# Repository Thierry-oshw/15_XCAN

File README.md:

# Can controller and CAN transceiver module

Can module to easily add CAN support to anything with SPI

[Link for controller](https://github.com/Thierry-oshw/17_CAN_Controller)

[Link for transceiver](https://github.com/Thierry-oshw/15_XCAN)

## Features
- Small (Controller is 18x20 mm, Transceiver is 17x15 mm)
- Cheap (2 layer and components on one side)
- 2.54 header + castellated pad for direct board to board soldering

## Made with

- [Kicad V6](https://www.kicad.org/)

## Schematic

### 15 XCAN Schematic

### 17 CAN Controller Schematic

## Build the PCB

PCB has been fully tested on multiple projects

[CAN Controller build files](https://github.com/Thierry-oshw/17_CAN_Controller/tree/main/fabrication_2023_04_23)

[CAN Transceiver build files without castellated holes](https://github.com/Thierry-oshw/15_XCAN/tree/main/fabrication_2023_04_21)

[CAN Transceiver build files with castellated holes](https://github.com/Thierry-oshw/15_XCAN/tree/main/fabrication_2023_04_21_CH)

## Authors

- Thierry Orlandi ([Hardware Freelance](https://www.linkedin.com/in/thierry-orlandi))
- Yohann Belair ([R&D Freelance](https://github.com/ciborg971))

## License
[CERN Open Hardware Licence Version 2](https://github.com/Thierry-oshw/15_XCAN/blob/main/LICENSE.txt)

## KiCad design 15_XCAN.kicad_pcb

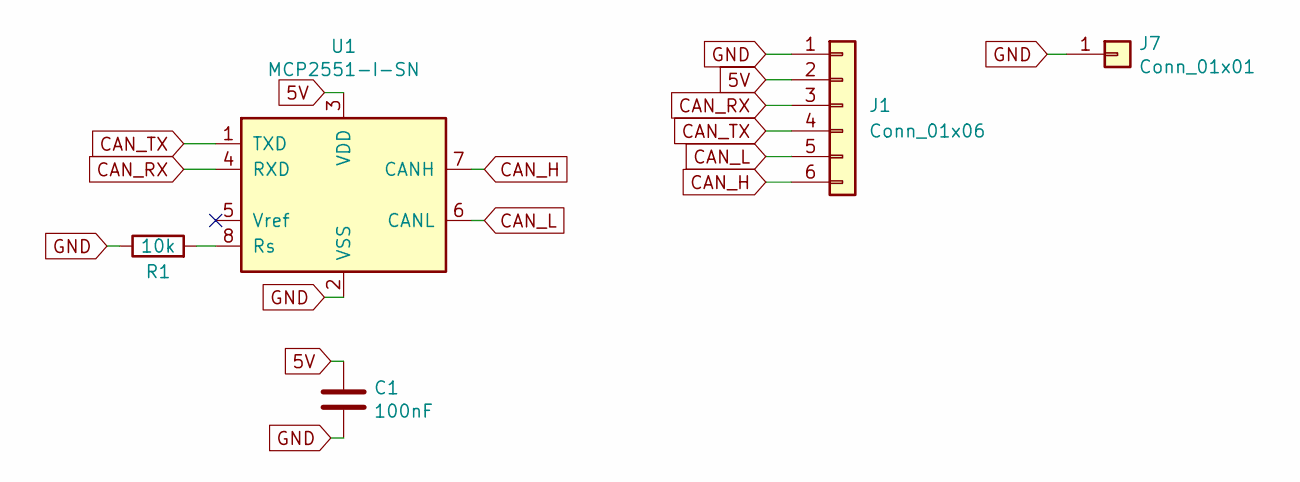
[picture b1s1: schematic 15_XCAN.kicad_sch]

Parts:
C1: 100nF; C_0603_1608Metric; LCSC C14663
J1: Conn_01x06; PinHeader_1x06_P2.54mm_Vertical
J7: Conn_01x01; PinHeader_1x01_P2.54mm_Vertical
R1: 10k; R_0603_1608Metric_Pad1.05x0.95mm_HandSolder; LCSC C25804
U1: MCP2551-I-SN; SOIC-8_3.9x4.9mm_P1.27mm; LCSC C49558

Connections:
5V: C1.1, J1.2, U1.3 (VDD)
CAN_H: J1.6, U1.7 (CANH)
CAN_L: J1.5, U1.6 (CANL)
CAN_RX: J1.3, U1.4 (RXD)
CAN_TX: J1.4, U1.1 (TXD)
GND: C1.2, J1.1, J7.1, R1.1, U1.2 (VSS)
unnamed: R1.2, U1.8 (Rs)

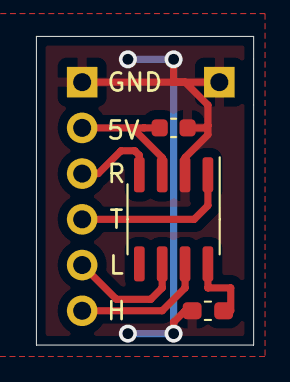
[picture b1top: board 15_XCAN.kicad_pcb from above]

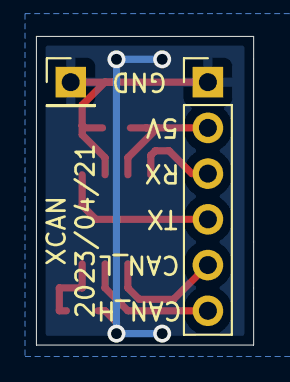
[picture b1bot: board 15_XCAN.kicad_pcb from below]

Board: 2 copper layers, 12.1 x 17.1 mm, 5 parts (2 on the bottom side), 7 nets.

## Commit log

2021-05-27 creation
    schema + routage
2021-07-26 maj split librairies
2022-10-30 maj kicad v6
2022-10-31 correction chemin model 3D
2022-11-02 réduction de taille du pcb
2022-11-02 maj step
    passage de wrl à step
    suppression de fichier.pro
2022-11-07 maj fichiers de fabrication
2022-11-09 Update 15_XCAN-top-pos.zip
    correction position soic8
2023-04-21 maj
    ajout sur silk
    changement sourcing jlcpcb
2023-04-21 version castellated holes
    rajout des castellated holes
2023-05-01 chgt fichier cern en licence
2023-05-02 maj readme
2023-05-28 maj readme : images 30 -> 50%
